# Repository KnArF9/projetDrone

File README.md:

# projetDrone
Projet électronique d'un drone
  - KiCad schéma, PCB
  - Rapport
  - Code tests unitaires

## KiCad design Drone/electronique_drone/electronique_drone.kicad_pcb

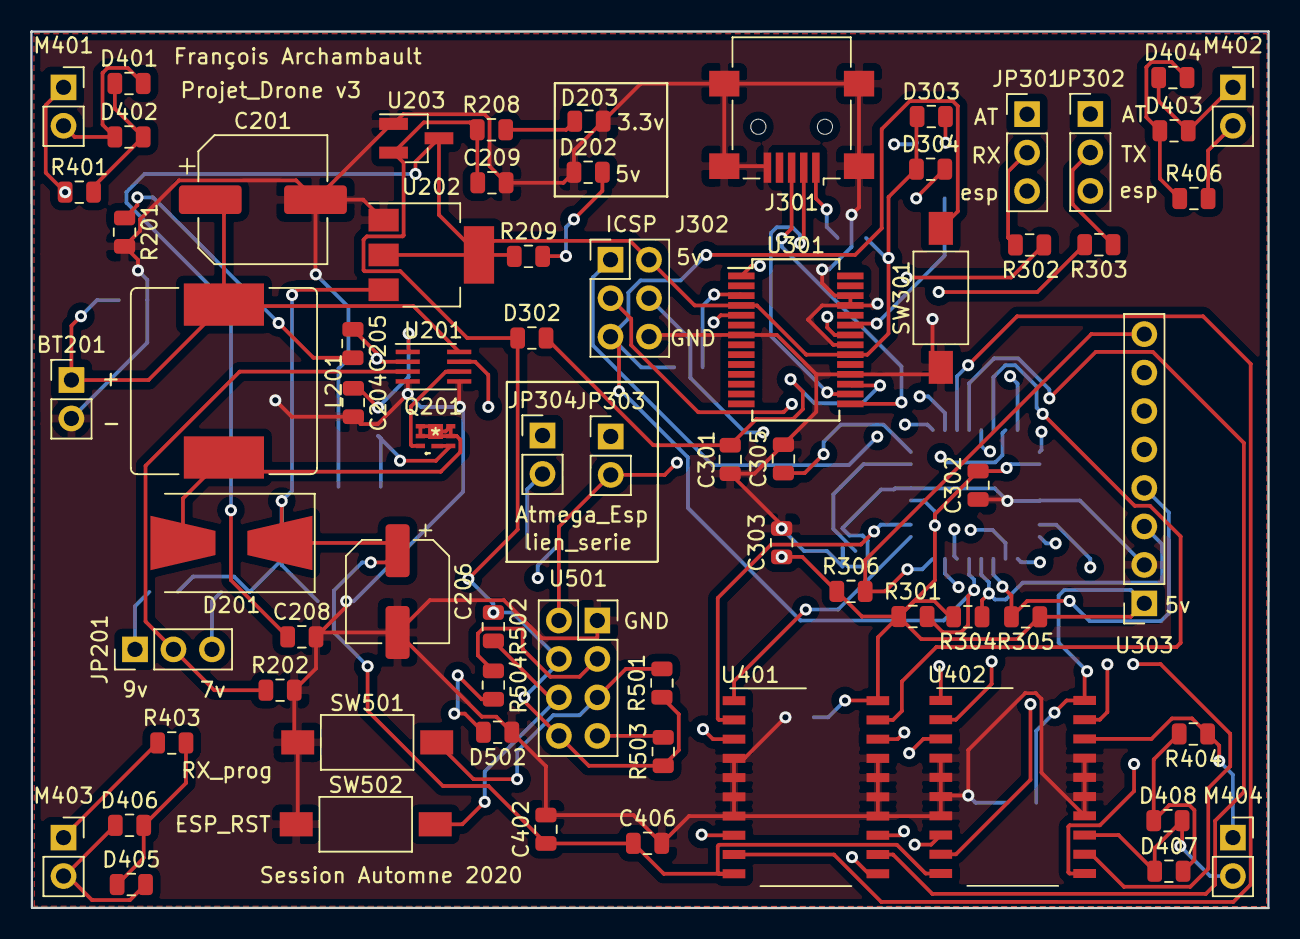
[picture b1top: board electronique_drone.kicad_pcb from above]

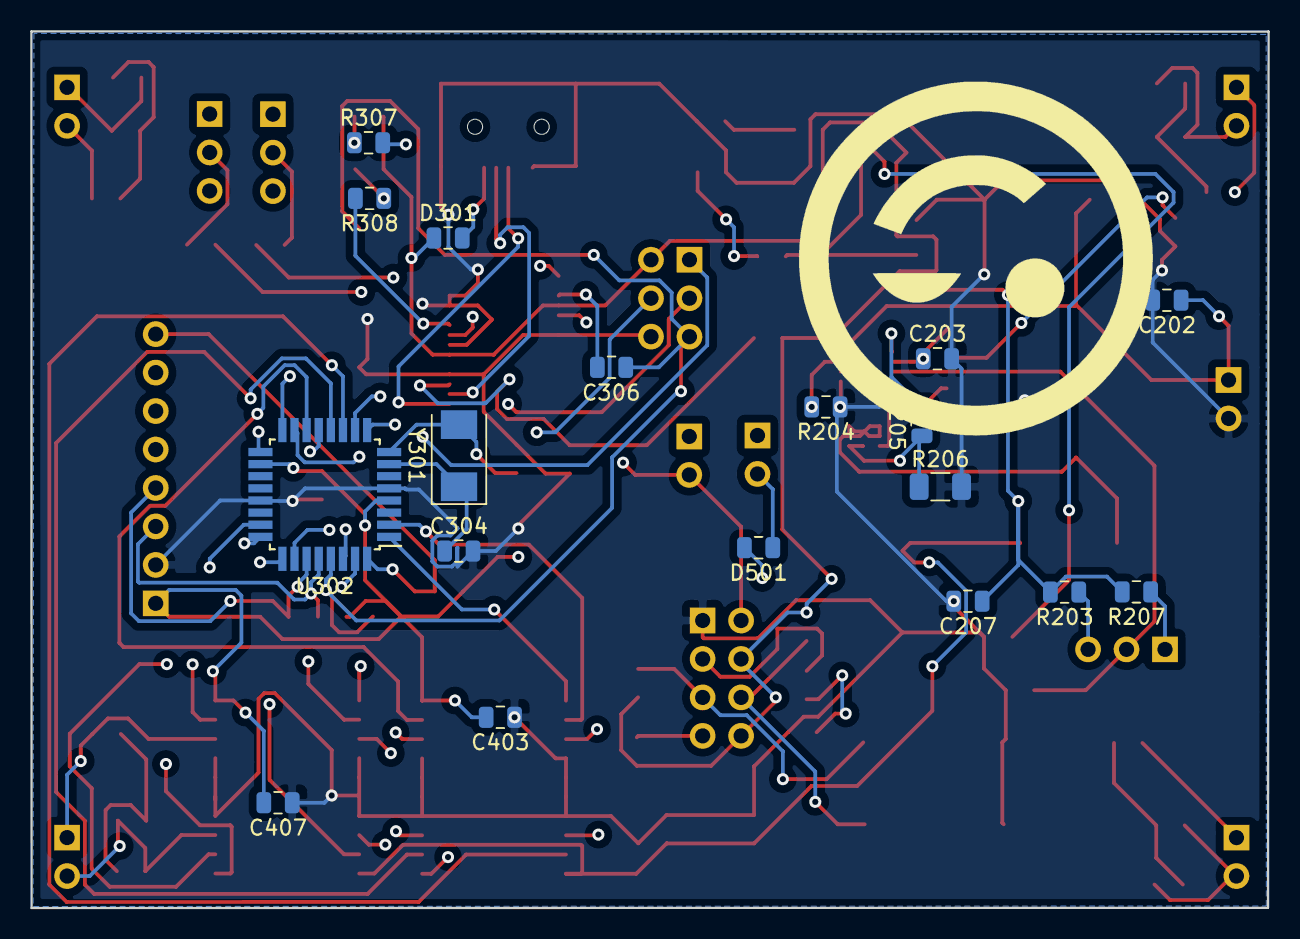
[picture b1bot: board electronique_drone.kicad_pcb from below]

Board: 4 copper layers, 81.7 x 57.9 mm, 88 parts (18 on the bottom side), 72 nets.

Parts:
BT201: Li-Po; PinHeader_1x02_P2.54mm_Vertical
C201: 470uF; CP_Elec_8x11.9
C202, C205: 100nF; R_0805_2012Metric
C203: 3.9nF; R_0805_2012Metric
C204: 10pF; R_0805_2012Metric
C206: 100uF; CP_Elec_6.3x3
C207: 0.33uF; R_0805_2012Metric
C208, C303, C306: 0.1uF; R_0805_2012Metric
C209: 2.2uF; R_0805_2012Metric
C301, C402, C403, C406, C407: 1uF; R_0805_2012Metric
C302: 4.7uF; R_0805_2012Metric
C304, C305: 22pF; R_0805_2012Metric
D201: B540C-13-F; D_SMB-SMC_Universal_Handsoldering
D202: del_5v; R_0805_2012Metric
D203: del_3.3; R_0805_2012Metric
D301, D302, D501: D_Schottky; R_0805_2012Metric
D303: delRX_rouge; R_0805_2012Metric
D304: DelTX_bleu; R_0805_2012Metric
D401, D404, D405, D408: DEL rouge; R_0805_2012Metric
D402, D403, D406, D407: DEL verte; R_0805_2012Metric
D502: LED_jaune_Tx; R_0805_2012Metric
J301: USB_B_Micro; USB_Mini-B_Lumberg_2486_01_Horizontal
J302: ICSP; PinHeader_2x03_P2.54mm_Vertical
JP201: 7v ou 9v; PinHeader_1x03_P2.54mm_Vertical
JP301: RX; PinHeader_1x03_P2.54mm_Vertical
JP302: TX; PinHeader_1x03_P2.54mm_Vertical
JP303: RXATmega_TXESP01; PinHeader_1x02_P2.54mm_Vertical
JP304: TXATmega_RXESP01; PinHeader_1x02_P2.54mm_Vertical
L201: 4.5uH; L_Bourns_SRR1210A
M401: M-Av-G; PinSocket_1x02_P2.54mm_Vertical
M402: M-Av-D; PinSocket_1x02_P2.54mm_Vertical
M403: M-Ar-G; PinSocket_1x02_P2.54mm_Vertical
M404: M-Ar-D; PinSocket_1x02_P2.54mm_Vertical
Q201: .; CSD13202Q2
R201: 1.58k; R_0805_2012Metric
R202: 1000; R_0805_2012Metric
R203: 4.53K; R_0805_2012Metric
R204: 26.7K; R_0805_2012Metric
R205: 100; R_0805_2012Metric
R206: 10m; R_1206_3216Metric
R207: 6.19k; R_0805_2012Metric
R208, R209, R307, R308, R401, R403, R404, R406, R504: 330; R_0805_2012Metric
R301, R304, R305, R306, R501, R502, R503: 4.7K; R_0805_2012Metric
R302, R303: 150; R_0805_2012Metric
SW301, SW501, SW502: SW_Push; SW_SPST_FSMSM
U201: LM3478; SSOP-8_2.95x2.8mm_P0.65mm
U202: LM1117-5.0; SOT-223-3_TabPin2
U203: AP2210; SOT-23_Handsoldering
U301: FT232RL; SSOP-28_5.3x10.2mm_P0.65mm
U302: ATmega328PB-AU; TQFP-32_7x7mm_P0.8mm
U303: GY-521; PinSocket_1x08_P2.54mm_Vertical
U401, U402: L293DD; SO-20_12.8x7.5mm_P1.27mm
U501: esp-01; PinSocket_2x04_P2.54mm_Vertical
Y301: 16Mhz; Crystal_SMD_Abracon_ABM3-2Pin_5.0x3.2mm

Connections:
+3.3v: C209.1, D302.1, R208.1, R501.1, R502.1, R503.1, U203.2, U501.4, U501.8
+4v: BT201.1, C201.1, C202.1, L201.1, U201.8
+5v: C208.1, C302.2, C303.1, C403.2, C407.2, D301.1, D303.1, D304.1, J302.2, R209.1, R301.1, R304.2, R305.1, R306.1, U202.2, U203.3, U301.4, U301.20, U302.4, U302.18, U303.1, U401.20, U402.20
+7v_+9v: C206.1, C207.1, C402.1, C406.1, D201.1, R203.2, R207.2, U202.3, U401.10, U402.10
/ESP01/ESP_RST: R502.2, SW502.2, U501.6
/ESP01/RX_ESP_3.3v: D501.2, R503.2, U501.7
/ESP01/RX_PROG: R501.2, SW501.2, U501.5
/MC/InterfaceProg/Capteur/A4(SDA): R305.2, U302.27, U303.4
/MC/InterfaceProg/Capteur/A5(SCL): R304.1, U302.28, U303.3
/MC/InterfaceProg/Capteur/D11: J302.4, U302.15
/MC/InterfaceProg/Capteur/D12: J302.1, U302.16
/MC/InterfaceProg/Capteur/D13: J302.3, U302.17
/MC/InterfaceProg/Capteur/INT0: R306.2, U302.32, U303.8
/MC/InterfaceProg/Capteur/RST: C306.2, J302.5, R301.2, SW301.2, U302.29
/MC/InterfaceProg/Capteur/RST_FT232: C306.1, U301.3
/MC/InterfaceProg/Capteur/RX_ATmega: JP301.1, JP303.1, U302.30
/MC/InterfaceProg/Capteur/TX_ATmega: JP302.1, JP304.1, U302.31
/MC/InterfaceProg/Capteur/rx_ft232: R307.2, U301.22
/MC/InterfaceProg/Capteur/tx_ft232: R308.2, U301.23
A0: U302.23, U402.9
A1: U302.24, U402.12
A2: U302.25, U402.19
A3: U302.26, U402.2
D3: U302.1, U401.1
D4: U302.2, U401.2
D5: U302.9, U401.11
D6: U302.10, U402.1
D7: U302.11, U401.9
D8: U302.12, U401.12
D9: U302.13, U402.11
D10: U302.14, U401.19
GND: BT201.2, C201.2, C202.2, C203.2, C204.2, C206.2, C207.2, C208.2, C209.2, C301.2, C302.1, C303.2, C304.2, C305.2, C402.2, C403.1, C406.2, C407.1, D202.1, D203.1, D502.1, J301.5, J301.6, J302.6, R201.2, R202.2, R204.1, R206.2, SW301.1, SW501.1, SW502.1, U201.4, U201.5, U202.1, U203.1, U301.7, U301.18, U301.21, U301.25, U301.26, U302.5, U302.21, U303.2, U401.4, U401.5, U401.6, U401.7, U401.14, U401.15, U401.16, U401.17, U402.4, U402.5, U402.6, U402.7, U402.14, U402.15, U402.16, U402.17, U501.1
Isen: C204.1, R205.2, U201.1
unnamed: C203.1, C205.1, U201.2
unnamed: C205.2, R201.1
unnamed: C301.1, D302.2, U301.17
unnamed: C304.1, U302.7, Y301.1
unnamed: C305.1, U302.8, Y301.2
unnamed: D201.2, L201.2, Q201.1, Q201.2, Q201.5, Q201.6, Q201.8
unnamed: D202.2, R209.2
unnamed: D203.2, R208.2
unnamed: D301.2, J301.1
unnamed: D303.2, R307.1
unnamed: D304.2, R308.1
unnamed: D401.1, D402.2, R401.2
unnamed: D401.2, D402.1, M401.2, U401.8
unnamed: D403.1, D404.2, R406.1
unnamed: D403.2, D404.1, M402.1, U401.18
unnamed: D405.1, D406.2, R403.2
unnamed: D405.2, D406.1, M403.2, U402.8
unnamed: D407.1, D408.2, M404.2, U402.13
unnamed: D407.2, D408.1, R404.2
unnamed: D502.2, R504.1
unnamed: J301.2, U301.16
unnamed: J301.3, U301.15
unnamed: JP201.1, R207.1
unnamed: JP201.2, R202.1, U201.3
unnamed: JP201.3, R203.1
unnamed: M401.1, R401.1, U401.3
unnamed: M402.2, R406.2, U401.13
unnamed: M403.1, R403.1, U402.3
unnamed: M404.1, R404.1, U402.18
unnamed: Q201.3, U201.6
unnamed: Q201.4, Q201.7, R205.1, R206.1
unnamed: R204.2, U201.7
unnamed: R302.2, U301.1
unnamed: R303.2, U301.5
unnamed: R504.2, U501.3
RX: JP301.2, R302.1
RX_ESP: D501.1, JP301.3, JP304.2
TX: JP302.2, R303.1
TX_ESP: JP302.3, JP303.2, U501.2

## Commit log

2020-10-29 Premier dépot
2021-01-19 projet fini!
